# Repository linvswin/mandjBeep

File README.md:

#### Working in progress !!!
# mandjBeep
## Cosa &egrave;? 
Centralina di allarme modulare pilotata da un atmega1284. 
### Storia
Il progetto &egrave; nato dall'esigenza di in stallare un sistema di allarme in casa. La prima bozza prevedeva l'uso di un atmega328, ma poi con crescere delle
funzionalit&agrave;, sono stato costretto a trovare un microcontrollore con un po di memoria in pi&ugrave;. La scelta &egrave; ricaduta su un atmega1284. Di seguito un comparazione 
tra i microcontrollori pi&ugrave; diffusi (Arduino like) 

<table>
	<tr><th>Feature</th><th>328P</th><th>1284P</th><th>2560P</th></tr>
	<tr><td>Price</td><td>$2.99</td><td>$4.66</td><td>$11.28</td></tr>
	<tr><td>RAM</td><td>2k</td><td>16k</td><td>8k</td></tr>
	<tr><td>Flash</td><td>32k</td><td>128k</td><td>256k</td></tr>
	<tr><td>EEPROM</td><td>1k</td><td>4k</td><td>4k</td></tr>
	<tr><td>UART</td><td>1</td><td>2</td><td>4</td></tr>
	<tr><td>IO Pins</td><td>23</td><td>32</td><td>86</td></tr>
	<tr><td>Interrupts</td><td>2</td><td>3</td><td>8</td></tr>
	<tr><td>Analog Inputs</td><td>6</td><td>8</td><td>16</td></tr>
</table>

### Caratteristiche:

* RTC: modulo DS3231 per la gestione del tempo
* LCD 20x4 per impostazioni/visualizzazione stato, etc (collegato ad un PCF8574 che lo rende I2C)
* tastierino 4x4 (tastierino a membrana classico x arduino collegato ad un PCF8574 che lo rende I2C)
* 2 zone (da implementare)
* avviso tramite modulo GSM (al momento solo tramite sms)
* relay per attivizione sirena.
* batteria tampone al piombo 12v 7A

## Librerie usate

* [Keypad_I2C](https://github.com/joeyoung/arduino_keypads/tree/master/Keypad_I2C): libreria per la gestione del tastierino I2C.
* [LCDMenuLib](https://github.com/Jomelo/LCDMenuLib): libreria per la gestione del menu.
* [secTimer](https://github.com/leomil72/secTimer): Simple seconds counter for Arduino boards and Atmel microcontrollers.
The library can count from 0 to (2^32)-1 seconds. This is a really HUGE
interval of time since (2^32)-1 seconds are about 136 years! So your
device will cease to function before the library will overflow!
* MandjTimer: modificato la libreria [Timer](http://playground.arduino.cc/Code/Timer) per utilizzare secTimer al posto di millis().
* [Password](http://playground.arduino.cc/Code/Password): libreria per la gestione del codice di accesso.
* [PCF8574](https://github.com/RobTillaart/Arduino/tree/master/libraries/PCF8574): libreria per la gestione dei moduli sensore, gestione dell'integrato PCF8574.
* [Rtc_by_Makuna](https://github.com/Makuna/Rtc): liberia per la gestione del modulo DS3231 pe la gestione del tempo.
* [TimerOneThree](https://github.com/heliosoph/TimerOneThree):  The arduino TimerOne library adapted for ATmega1284P and extended for timer3.
* [GSM Shield](http://www.gsmlib.org): a library developed for Arduino's shields that support SIM900/SIM908.
* [Keypad](http://playground.arduino.cc/Code/Keypad): a library for using <em>matrix</em> style keypads with the Arduino. As of version 3.0 it now supports mulitple keypresses.
* [NewLiquidCrystal](https://bitbucket.org/fmalpartida/new-liquidcrystal/wiki/Home): the <em>LCD Library</em> for <strong>Arduino</strong> and <strong>Chipkit</strong>. It is a derivate of the original LiquidCrystal Library as sourced in the Arduino SDK. It has been developed to be compatible with the current LiquidCrystal library, its performance is almost 5 times faster and fully extendable if need be.
* [SoftwareSerial](https://www.arduino.cc/en/Reference/SoftwareSerial): library has been developed to allow serial communication on other digital pins of the Arduino, using software to replicate the functionality.
* [Wire](https://www.arduino.cc/en/Reference/Wire): library allows you to communicate with <span class="wikiword">I2C</span> / TWI devices.
 
##  Author

* M&J 
* Sito: [siatienfalla](http://siatienfalla.altervista.org/)
* Data inizio: 09/02/2016
* Versione: 1.0
 
## Licence: GPL ver. 3

## Immagini

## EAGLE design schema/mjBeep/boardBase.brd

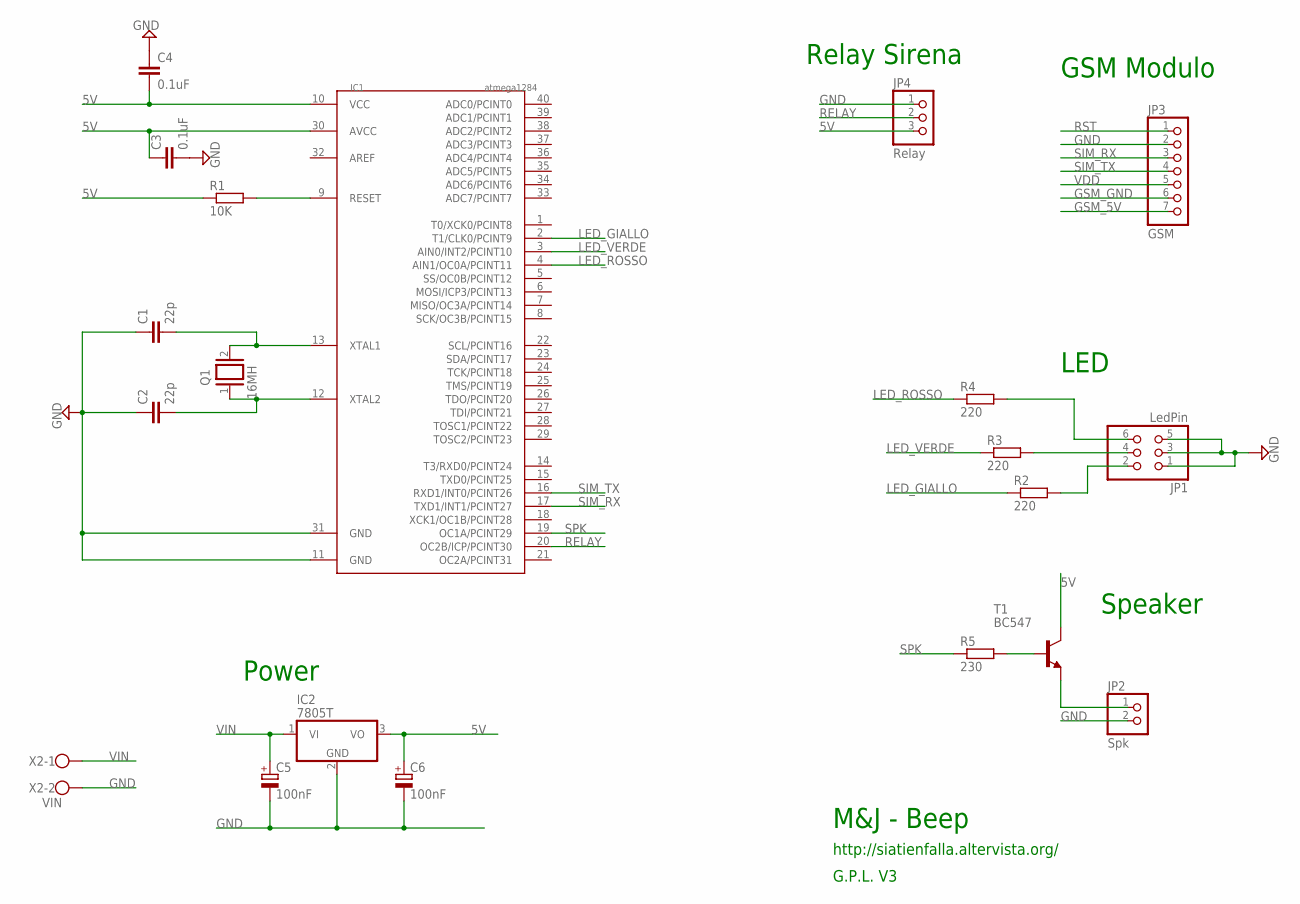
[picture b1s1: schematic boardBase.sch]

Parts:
C1, C2: 22p; C025-024X044
C3, C4: 0.1uF; C025-025X050
C5, C6: 100nF; E3,5-10
IC1: atmega1284; DIL40
IC2: 7805T; TO220H
JP1: LedPin; 2X03
JP2: Spk; 1X02
JP3: GSM; 1X07
JP4: Relay; 1X03
Q1: 16MH; QS
R1: 10K; 0207/10
R2, R3, R4: 220; 0207/10
R5: 230; 0207/10
T1: BC547; TO92
X2: VIN; W237-102

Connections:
5V: C3.1, C4.2, C6.+, IC1.10 (VCC), IC1.30 (AVCC), IC2.3 (VO), JP4.3, R1.1, T1.3 (C)
GND: C1.1, C2.1, C3.2, C4.1, C5.-, C6.-, IC1.11 (GND), IC1.31 (GND), IC2.2 (GND), JP1.1, JP1.3, JP1.5, JP2.2, JP3.2, JP4.1, X2.2
GSM_5V: JP3.7
GSM_GND: JP3.6
LED_GIALLO: IC1.2 (T1/CLK0/PCINT9), R2.1
LED_ROSSO: IC1.4 (AIN1/OC0A/PCINT11), R4.1
LED_VERDE: IC1.3 (AIN0/INT2/PCINT10), R3.1
unnamed: C2.2, IC1.12 (XTAL2), Q1.1
unnamed: C1.2, IC1.13 (XTAL1), Q1.2
unnamed: IC1.9 (RESET), R1.2
unnamed: JP1.2, R2.2
unnamed: JP1.4, R3.2
unnamed: JP1.6, R4.2
unnamed: R5.2, T1.2 (B)
unnamed: JP2.1, T1.1 (E)
RELAY: IC1.20 (OC2B/ICP/PCINT30), JP4.2
RST: JP3.1
SIM_RX: IC1.17 (TXD1/INT1/PCINT27), JP3.3
SIM_TX: IC1.16 (RXD1/INT0/PCINT26), JP3.4
SPK: IC1.19 (OC1A/PCINT29), R5.1
VDD: JP3.5
VIN: C5.+, IC2.1 (VI), X2.1

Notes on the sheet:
Speaker
Relay Sirena
LED
Power
GSM Modulo
M&J - Beep
http://siatienfalla.altervista.org/
G.P.L. V3

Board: 2 copper layers, 20 parts (0 on the bottom side), 18 nets, no tracks yet.

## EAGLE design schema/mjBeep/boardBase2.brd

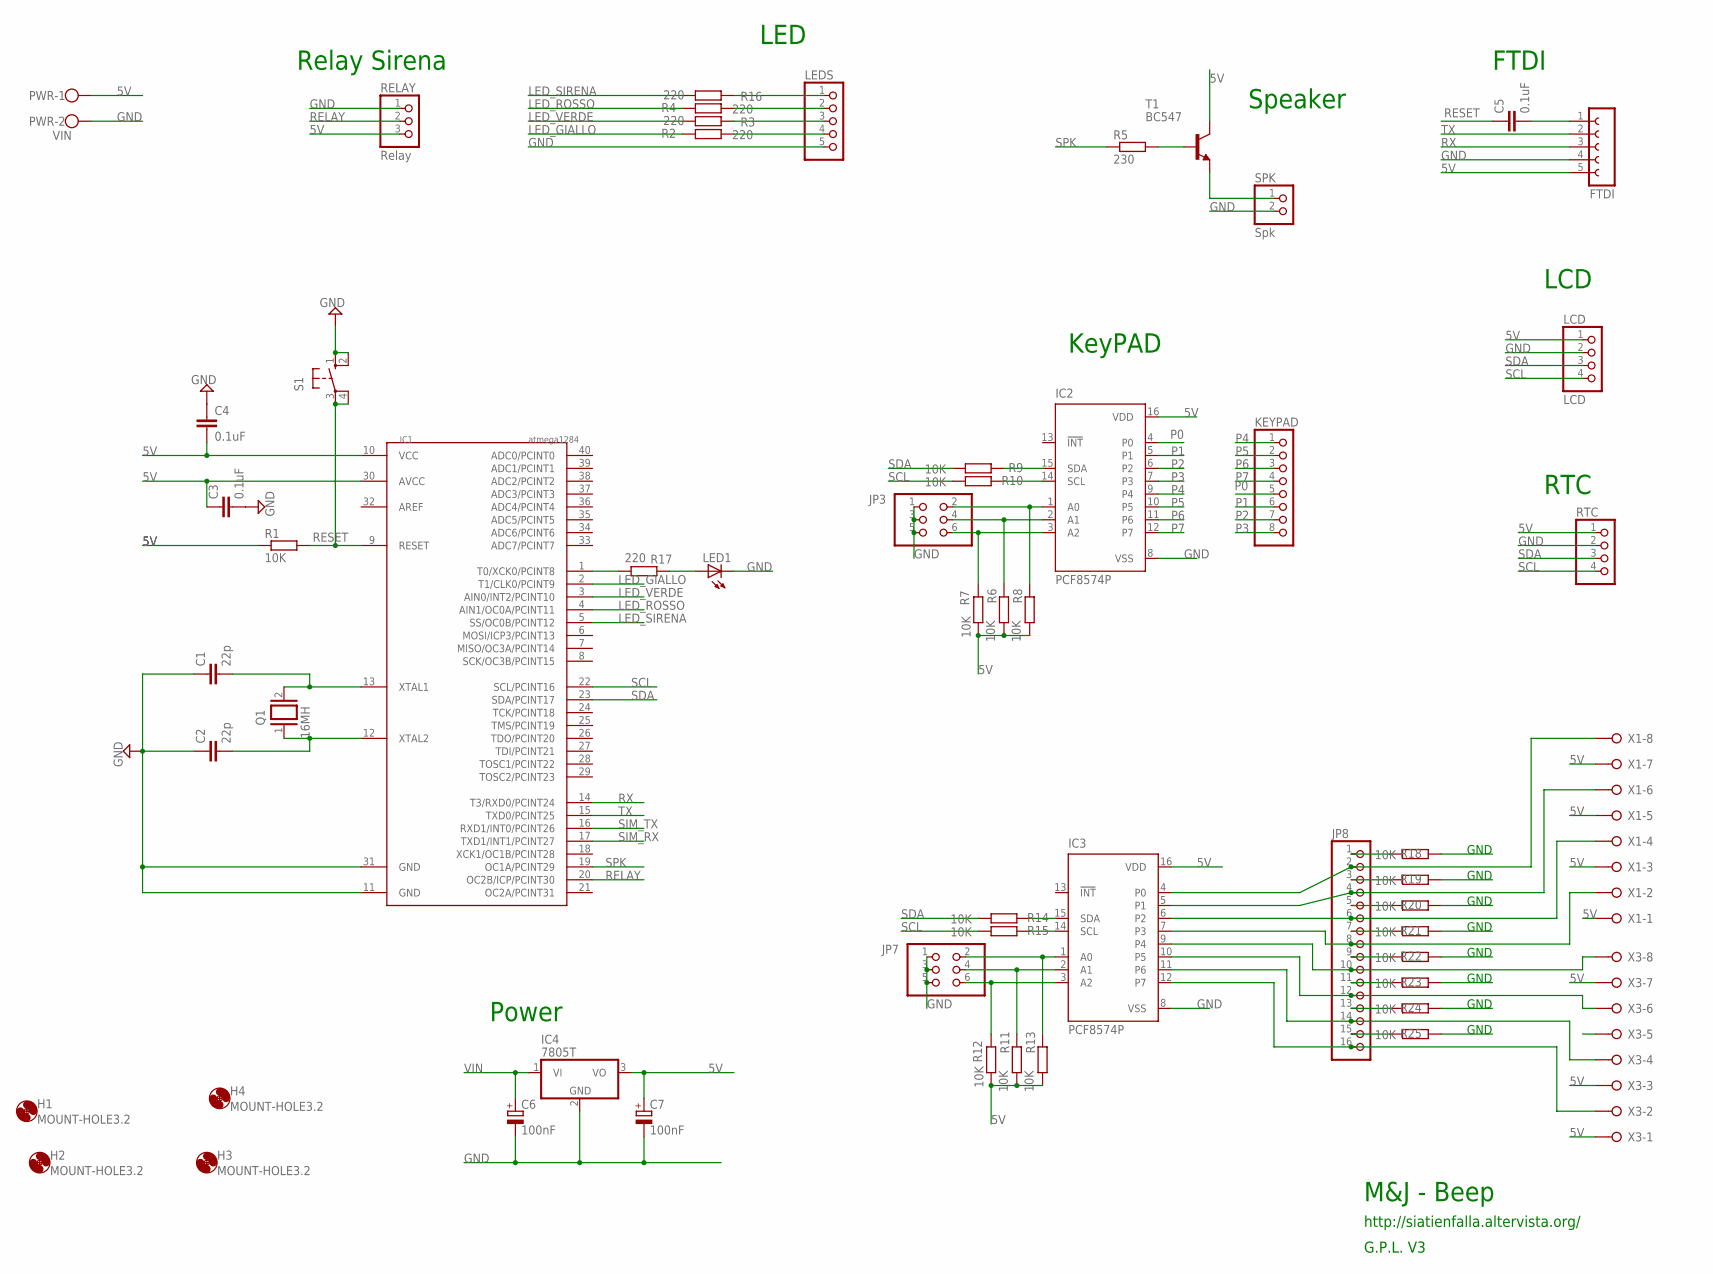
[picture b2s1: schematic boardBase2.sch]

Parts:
C1, C2: 22p; C025-024X044
C3, C4, C5: 0.1uF; C025-025X050
C6, C7: 100nF; E3,5-10
FTDI: FE05-1
H1, H2, H3, H4: MOUNT-HOLE3.2; 3,2
IC1: atmega1284; DIL40
IC2, IC3: PCF8574P; DIL16
IC4: 7805T; TO220H
JP3, JP7: PINHD-2X3; 2X03
JP8: PINHD-1X16; 1X16
KEYPAD: PINHD-1X8; 1X08
LCD: LCD; 1X04
LED1: LED3MM
LEDS: PINHD-1X5; 1X05
PWR: VIN; W237-102
Q1: 16MH; QS
R1, R6, R7, R8, R9, R10: 10K; 0207/10
R2, R3, R4, R16, R17: 220; 0207/2V
R5: 230; 0207/10
R11, R12, R13, R14, R15, R18, R19, R20, R21, R22, R23, R24, R25: 10K; 0207/2V
RELAY: Relay; 1X03
RTC: PINHD-1X4; 1X04
S1: 10-XX; B3F-10XX
SPK: Spk; 1X02
T1: BC547; TO92
X1, X3: W237-08P; W237-8P

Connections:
5V: C3.1, C4.2, C7.+, FTDI.5, IC1.10 (VCC), IC1.30 (AVCC), IC2.16 (VDD), IC3.16 (VDD), IC4.3 (VO), LCD.1, PWR.1, R1.1, R6.1, R7.2, R8.1, R11.1, R12.2, R13.1, RELAY.3, RTC.1, T1.3 (C), X1.1, X1.3, X1.5, X1.7, X3.1, X3.3, X3.5, X3.7
GND: C1.1, C2.1, C3.2, C4.1, C6.-, C7.-, FTDI.4, IC1.11 (GND), IC1.31 (GND), IC2.8 (VSS), IC3.8 (VSS), IC4.2 (GND), JP3.1, JP3.3, JP3.5, JP7.1, JP7.3, JP7.5, LCD.2, LED1.K (C), LEDS.5, PWR.2, R18.1, R19.1, R21.1, R22.1, R23.1, R24.1, R25.1, RELAY.1, RTC.2, S1.1 (S), S1.2 (S1), SPK.2
LED_GIALLO: IC1.2 (T1/CLK0/PCINT9), R2.2
LED_ROSSO: IC1.4 (AIN1/OC0A/PCINT11), R4.2
LED_SIRENA: IC1.5 (SS/OC0B/PCINT12), R16.1
LED_VERDE: IC1.3 (AIN0/INT2/PCINT10), R3.1
unnamed: C2.2, IC1.12 (XTAL2), Q1.1
unnamed: C1.2, IC1.13 (XTAL1), Q1.2
unnamed: IC2.1 (A0), JP3.2, R8.2
unnamed: C5.2, FTDI.1
unnamed: IC2.2 (A1), JP3.4, R6.2
unnamed: IC2.3 (A2), JP3.6, R7.1
unnamed: LEDS.4, R2.1
unnamed: LEDS.3, R3.2
unnamed: LEDS.2, R4.1
unnamed: IC2.14 (SCL), R10.1
unnamed: R5.2, T1.2 (B)
unnamed: SPK.1, T1.1 (E)
unnamed: IC2.15 (SDA), R9.1
unnamed: IC3.1 (A0), JP7.2, R13.2
unnamed: IC3.2 (A1), JP7.4, R11.2
unnamed: IC3.3 (A2), JP7.6, R12.1
unnamed: IC3.14 (SCL), R15.1
unnamed: IC3.15 (SDA), R14.1
unnamed: LEDS.1, R16.2
unnamed: IC1.1 (T0/XCK0/PCINT8), R17.1
unnamed: LED1.A, R17.2
unnamed: IC3.4 (P0), JP8.2, X1.8
unnamed: IC3.5 (P1), JP8.4, X1.6
unnamed: IC3.6 (P2), JP8.6, X1.4
unnamed: IC3.7 (P3), JP8.8, X1.2
unnamed: IC3.9 (P4), JP8.10, X3.8
unnamed: IC3.10 (P5), JP8.12, X3.6
unnamed: IC3.11 (P6), JP8.14, X3.4
unnamed: IC3.12 (P7), JP8.16, X3.2
unnamed: JP8.1, R18.2
unnamed: JP8.3, R19.2
unnamed: JP8.5, R20.2
unnamed: JP8.7, R21.2
unnamed: JP8.9, R22.2
unnamed: JP8.11, R23.2
unnamed: JP8.13, R24.2
unnamed: JP8.15, R25.2
P0: IC2.4 (P0), KEYPAD.5
P1: IC2.5 (P1), KEYPAD.6
P2: IC2.6 (P2), KEYPAD.7
P3: IC2.7 (P3), KEYPAD.8
P4: IC2.9 (P4), KEYPAD.1
P5: IC2.10 (P5), KEYPAD.2
P6: IC2.11 (P6), KEYPAD.3
P7: IC2.12 (P7), KEYPAD.4
RELAY: IC1.20 (OC2B/ICP/PCINT30), RELAY.2
RESET: C5.1, IC1.9 (RESET), R1.2, S1.3, S1.4 (P1)
RX: FTDI.3, IC1.14 (T3/RXD0/PCINT24)
SCL: IC1.22 (SCL/PCINT16), LCD.4, R10.2, R15.2, RTC.4
SDA: IC1.23 (SDA/PCINT17), LCD.3, R9.2, R14.2, RTC.3
SIM_RX: IC1.17 (TXD1/INT1/PCINT27)
SIM_TX: IC1.16 (RXD1/INT0/PCINT26)
SPK: IC1.19 (OC1A/PCINT29), R5.1
TX: FTDI.2, IC1.15 (TXD0/PCINT25)
VIN: C6.+, IC4.1 (VI)

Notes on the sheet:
Speaker
Relay Sirena
LED
M&J - Beep
http://siatienfalla.altervista.org/
G.P.L. V3
FTDI
KeyPAD
GND
RTC
LCD
Power

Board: 2 copper layers, 57 parts (1 on the bottom side), 59 nets, no tracks yet.

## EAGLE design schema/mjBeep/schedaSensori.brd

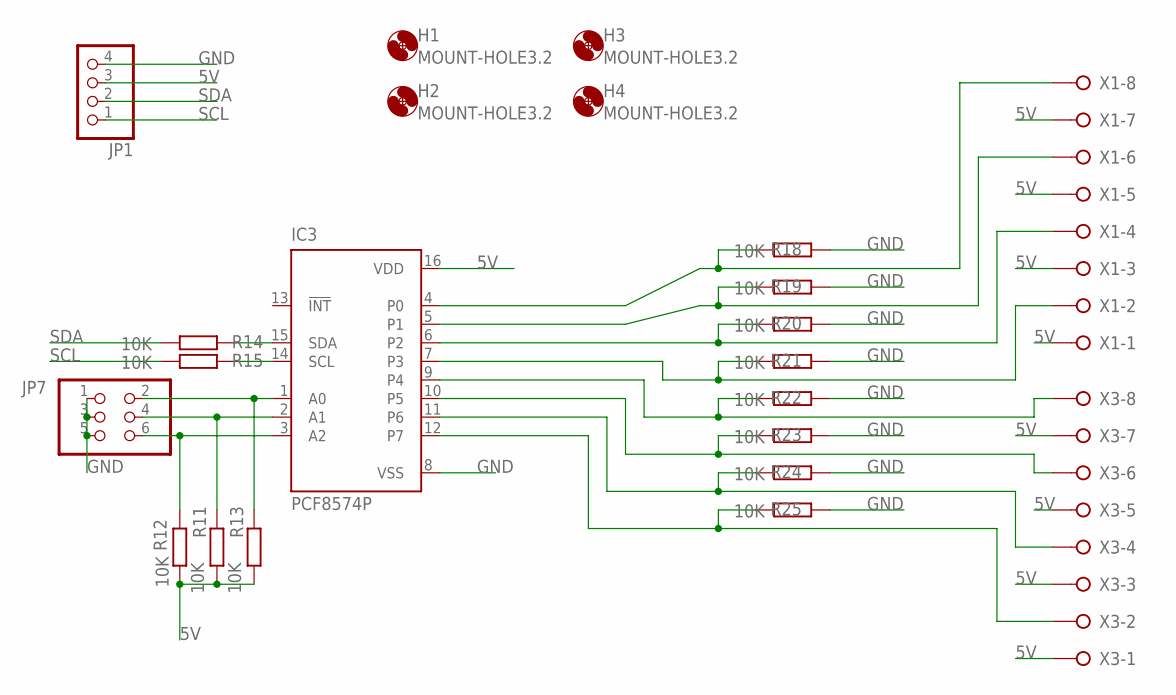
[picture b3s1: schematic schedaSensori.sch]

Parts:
H1, H2, H3, H4: MOUNT-HOLE3.2; 3,2
IC3: PCF8574P; DIL16
JP1: PINHD-1X4; 1X04
JP7: PINHD-2X3; 2X03
R11, R12, R13, R14, R15, R18, R19, R20, R21, R22, R23, R24, R25: 10K; 0207/10
X1, X3: W237-08P; W237-8P

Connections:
5V: IC3.16 (VDD), JP1.3, R11.1, R12.2, R13.1, X1.1, X1.3, X1.5, X1.7, X3.1, X3.3, X3.5, X3.7
GND: IC3.8 (VSS), JP1.4, JP7.1, JP7.3, JP7.5, R18.1, R19.1, R20.1, R21.1, R22.1, R23.1, R24.1, R25.1
unnamed: IC3.1 (A0), JP7.2, R13.2
unnamed: IC3.2 (A1), JP7.4, R11.2
unnamed: IC3.3 (A2), JP7.6, R12.1
unnamed: IC3.14 (SCL), R15.1
unnamed: IC3.15 (SDA), R14.1
unnamed: IC3.4 (P0), R18.2, X1.8
unnamed: IC3.5 (P1), R19.2, X1.6
unnamed: IC3.6 (P2), R20.2, X1.4
unnamed: IC3.7 (P3), R21.2, X1.2
unnamed: IC3.9 (P4), R22.2, X3.8
unnamed: IC3.10 (P5), R23.2, X3.6
unnamed: IC3.11 (P6), R24.2, X3.4
unnamed: IC3.12 (P7), R25.2, X3.2
SCL: JP1.1, R15.2
SDA: JP1.2, R14.2

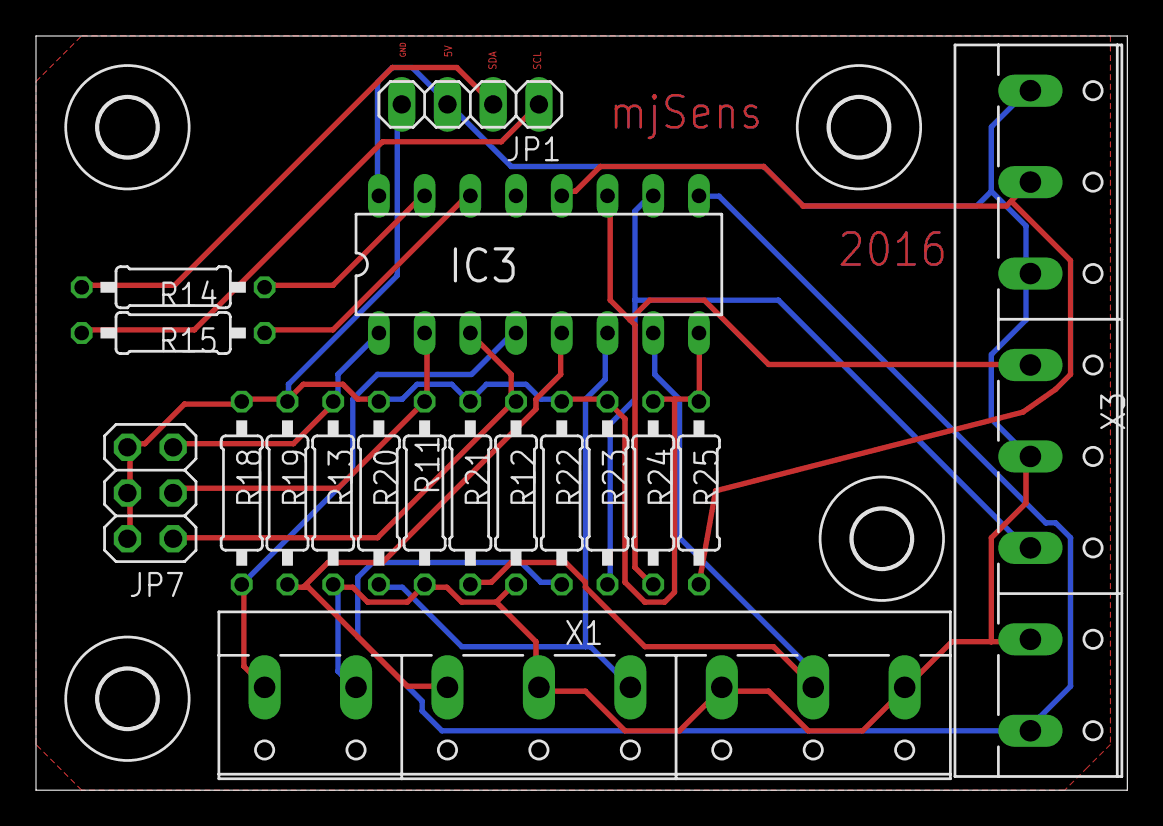
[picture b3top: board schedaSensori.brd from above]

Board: 2 copper layers, 60.6 x 41.9 mm, 22 parts (0 on the bottom side), 17 nets.

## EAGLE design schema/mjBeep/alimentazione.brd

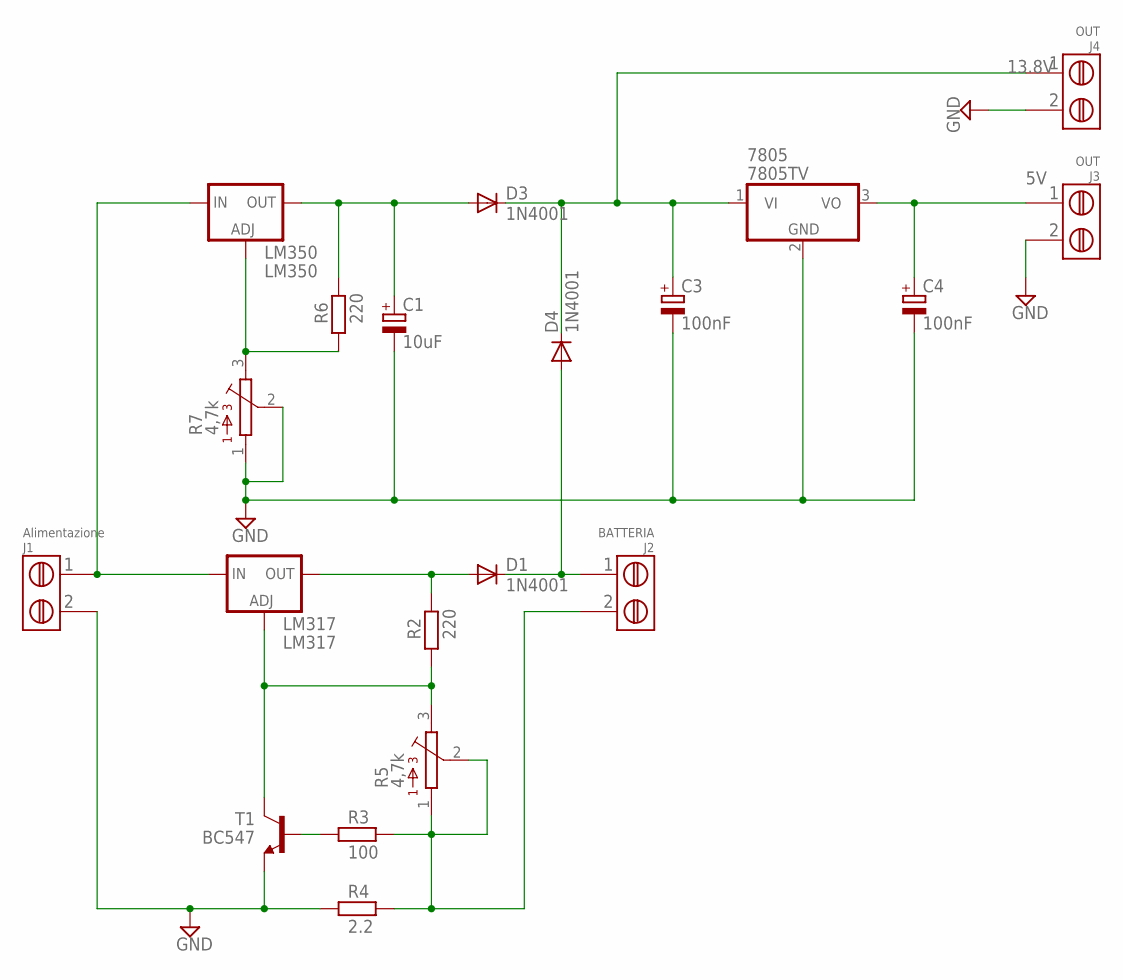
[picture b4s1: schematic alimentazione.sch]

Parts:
7805: 7805TV; TO220V
C1: 10uF; E2,5-6
C3, C4: 100nF; E2,5-6
D1, D3, D4: 1N4001; DO41-10
J1: Alimentazione; MORSETTIERA
J2: BATTERIA; MORSETTIERA
J3, J4: OUT; MORSETTIERA
LM317: LM317; 317TS
LM350: LM350; 317TS
R2, R6: 220; R1/4W
R3: 100; R1/4W
R4: 2.2; R1/4W
R5, R7: 4,7k; CA9V
T1: BC547; TO92

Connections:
5V: 7805.3 (VO), C4.+, J3.1
13.8V: 7805.1 (VI), C3.+, D3.C (K), D4.C (K), J4.1
+BAT: D1.C (K), D4.A, J2.1
-BAT: J2.2, R3.2, R4.2, R5.1, R5.2
GND: 7805.2 (GND), C1.-, C3.-, C4.-, J1.2, J3.2, J4.2, R4.1, R7.1, R7.2, T1.1 (E)
unnamed: C1.+, D3.A, LM350.2 (OUT), R6.2
unnamed: R3.1, T1.2 (B)
unnamed: LM350.1 (ADJ), R6.1, R7.3
unnamed: J1.1, LM317.3 (IN), LM350.3 (IN)
unnamed: D1.A, LM317.2 (OUT), R2.2
unnamed: LM317.1 (ADJ), R2.1, R5.3, T1.3 (C)

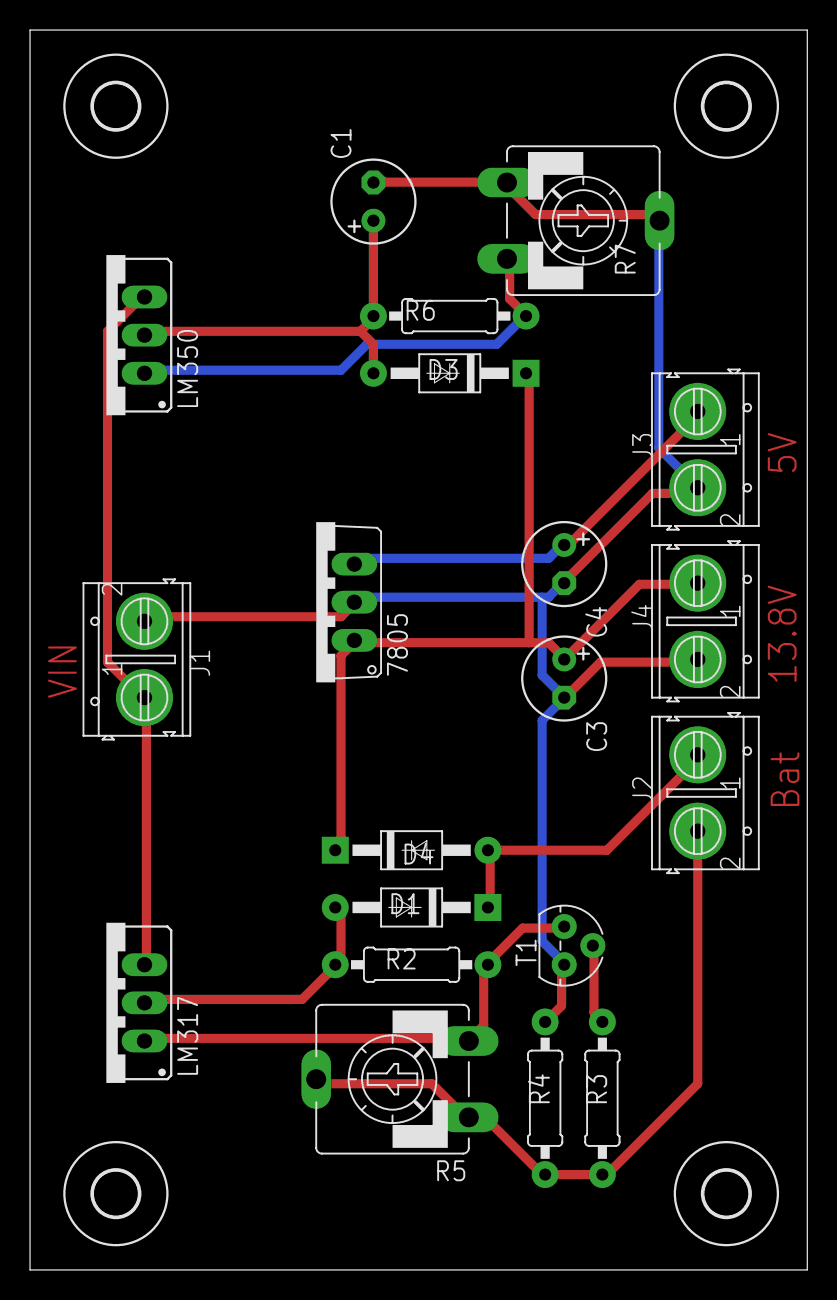
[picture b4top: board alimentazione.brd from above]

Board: 2 copper layers, 51.7 x 82.5 mm, 24 parts (0 on the bottom side), 11 nets.

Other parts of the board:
U$1, U$2, U$3, U$4: 3,0

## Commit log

2016-03-07 Added files via upload
2016-03-07 primo invio
2016-03-07 file definizioni funzioni
2016-03-07 file configurazioni
2016-03-07 Cambiato nome alla classa PCF8574 perchè una libreria usava stasso nome per una variabile
2016-03-07 Configurazione getsione del menu
2016-03-07 File principale
2016-03-07 File compatibilità con IDE Arduino
2016-03-07 add settings
2016-03-07 aggiunta F() a delle stringe define
2016-03-08 cambio modalità di impostazione dei pin, usando accesso registro diretto
2016-03-09 librerie
2016-03-09 spostati in lib
2016-03-11 Schemi elettronici
2016-05-21 corretto check sensori: setto stato sensAttivo ai sensori con stato SensMalfunzionamento prima di verificarne lo stato
2016-06-01 app per gestione remoto (ricordarsi di impostare lingua "Italiano" in appInventor)
2016-06-07 app image
2016-12-10 mod gestione tempo ritardo sensori
2016-12-10 Modifiche per la gestione del ritardo qunado un sensore rileva un infrazione
2022-08-19 - definizione funzione printerttings
2022-08-21 - modifiche schema fritz
2022-08-21 - eliminati erori del merge
2022-08-22 - estesa classe LiquidCrystal_I2C - creata proprietà lcd in MjBeep
2022-08-22 - spostati definizione del settings e dei sensore dal file MandJBepp.h al file pin.h
2022-08-22 - creata classe Clock che si accupa del tempo
